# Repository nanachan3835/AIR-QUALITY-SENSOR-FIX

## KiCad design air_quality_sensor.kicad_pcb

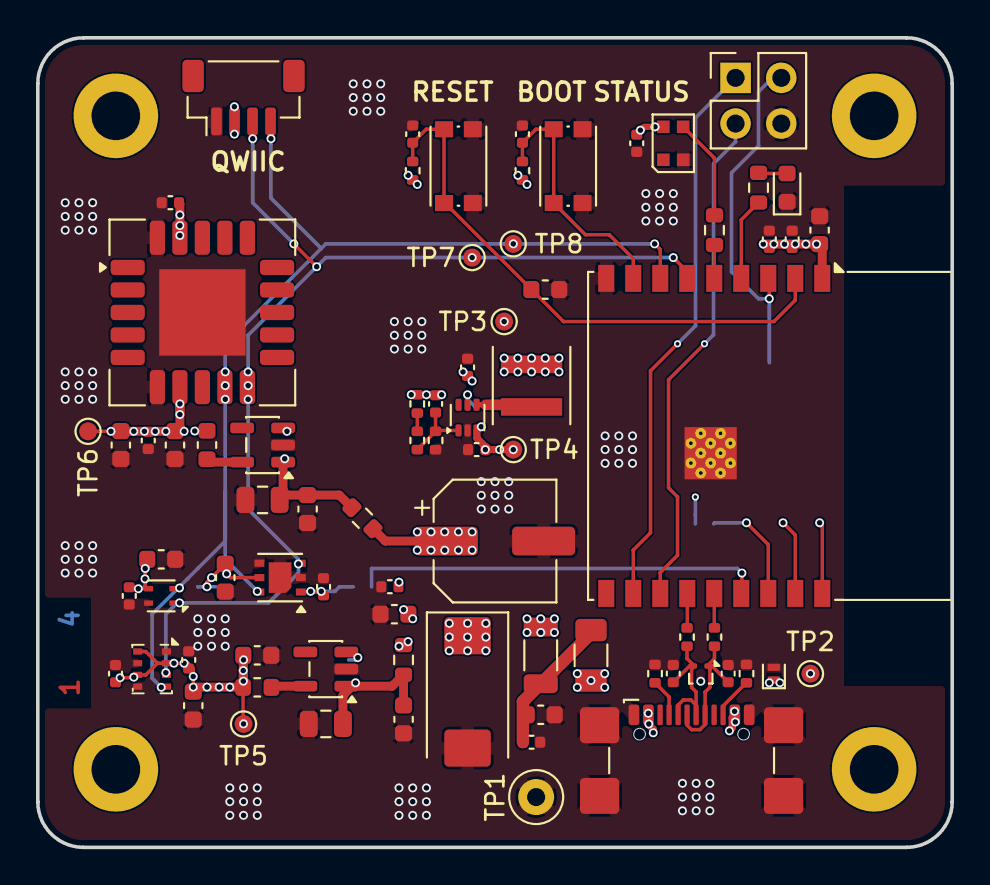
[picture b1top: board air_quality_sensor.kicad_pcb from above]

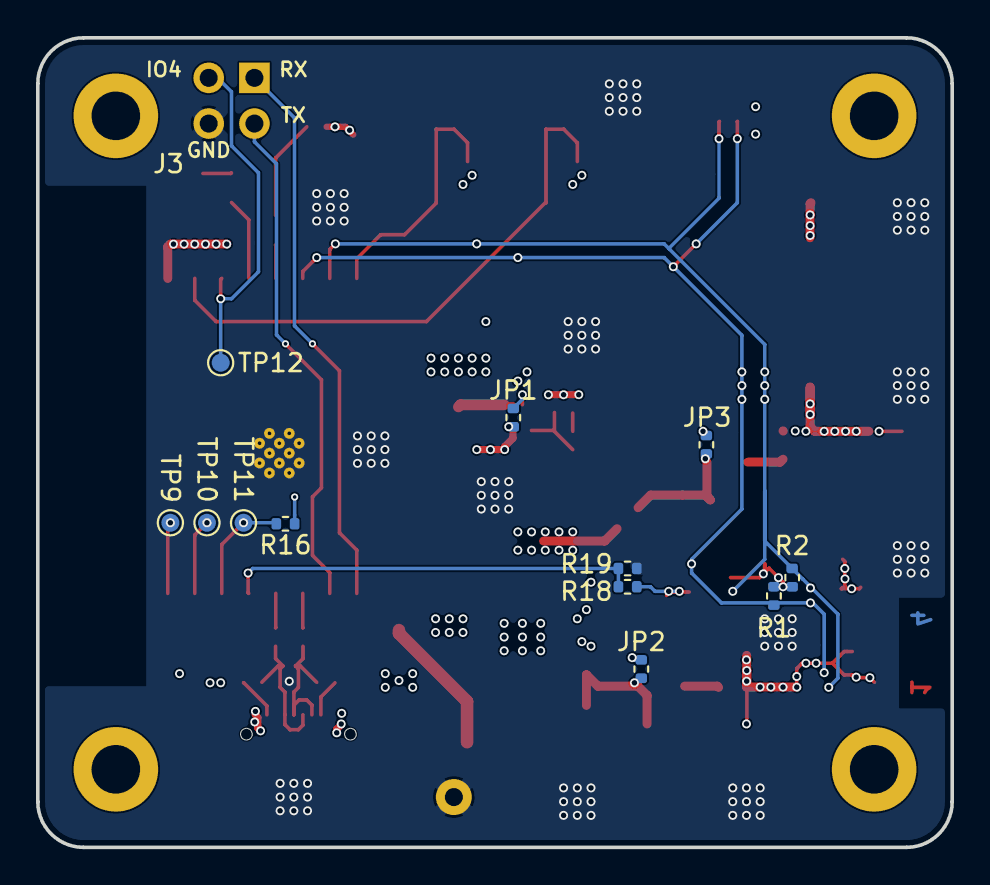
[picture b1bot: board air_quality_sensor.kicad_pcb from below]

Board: 4 copper layers, 50.8 x 45.0 mm, 93 parts (12 on the bottom side), 38 nets.

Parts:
C1: 4.7µ/10V/X5R; C_0402_1005Metric
C2, C3, C5, C12, C13, C21, C22, C25, C30, C31, C34: 100n/10V/X5R; C_0402_1005Metric
C4, C9, C10: 10p/10V/C0G; C_0402_1005Metric
C6, C29: 22µ/10V/X5R; C_0402_1005Metric
C7, C8, C11, C17, C18, C19, C20, C24, C26, C28, C32, C33: 1µ/10V/X5R; C_0603_1608Metric
C14, C27: 47µ/10V/X5R; C_0805_2012Metric
C15: 100µ/16V; CP_EIA-7343-20_Kemet-V
C16: 1µ/10V/X5R; C_0402_1005Metric
C23: 47u/16V/20%; CP_Elec_6.3x7.7
D1: ESDALC5; D_SOD-882
D2: LED 0603 red; LED_0603_1608Metric
D3: WS2812; LED_WS2812B-2020_PLCC4_2.0x2.0mm
F1: PPTC 8V 750mA; Fuse_1206_3216Metric
FB1, FB3: 0R; L_0603_1608Metric
FB2: 1k@100MHz; L_1206_3216Metric
H1, H2, H3, H4: M3_MountingHole; MountingHole_2.7mm_M2.5_DIN965_Pad
J1: USB4110; USB_C_Receptacle_GCT_USB4110
J2: QWIIC Connector; JST_SH_BM04B-SRSS-TB_1x04-1MP_P1.00mm_Vertical
J3: Conn_02x02_Odd_Even; PinHeader_2x02_P2.54mm_Vertical
JP1, JP2, JP3: 0/1%; R_0402_1005Metric
L1: 1uH/20%/9.6A; L_Coilcraft_XxL4020
R1, R2: 4.7k/1%; R_0402_1005Metric
R3, R9: 22/1%; R_0402_1005Metric
R4, R5: 5.1k/1%; R_0402_1005Metric
R6: 270k/1%; R_0402_1005Metric
R7: 180k/1%; R_0402_1005Metric
R8: 100k/1%; R_0402_1005Metric
R10, R12: 330/1%; R_0603_1608Metric
R11: 36/1%; R_0603_1608Metric
R13: 0/1%; R_0603_1608Metric
R14, R15, R18, R19: 10k/1%; R_0402_1005Metric
R16: 10K; R_0402_1005Metric
SW1, SW2: Push_Button; SW_Push_1P1T_NO_CK_KMR2
TP1: GND; TestPoint_Loop_D2.50mm_Drill1.0mm
TP2: VBUS; TestPoint_Pad_D1.0mm
TP3: +3V3; TestPoint_Pad_D1.0mm
TP4: 5V; TestPoint_Pad_D1.0mm
TP5: +3V3_SENS; TestPoint_Pad_D1.0mm
TP6: 3V3_SCD; TestPoint_Pad_D1.0mm
TP7: SDA; TestPoint_Pad_D1.0mm
TP8: SCL; TestPoint_Pad_D1.0mm
TP9: IO0; TestPoint_Pad_D1.0mm
TP10: IO1; TestPoint_Pad_D1.0mm
TP11: IO2; TestPoint_Pad_D1.0mm
TP12: ADC1_CH4; TestPoint_Pad_D1.0mm
U1: TLV62569A; SOT-563
U2: SHT40; Sensirion_DFN-4_1.5x1.5mm_P0.8mm_SHT4x_NoCentralPad
U3: BMP280; Bosch_LGA-8_2x2.5mm_P0.65mm_ClockwisePinNumbering
U4: TPD2EUSB30; Texas_DRT-3
U5: SCD41; Sensirion_SCD4x-1EP_10.1x10.1mm_P1.25mm_EP4.8x4.8mm
U6: SGP41; XDCR_SGP41-D-R4
U7: TPS7A20; SOT-23-5
U8: ESP32-C3-WROOM-02
U9: TLV75533P; SOT-23-5

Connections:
+3V3: C6.1, C10.1, C29.1, C31.1, C33.1, J2.2, L1.2, R6.1, R14.1, R15.1, R16.1, TP3.1 (1_1), U8.1 (3V3)
+3V3_SCD: C13.1, C18.1, C32.1, C34.1, FB1.2, TP6.1 (1_1), U5.7 (VDD), U5.19 (VDD)
+3V3_SENS: C2.1, C3.1, C5.1, C7.1, C8.1, C16.1, C20.1, C24.1, FB3.2, R1.1, R2.1, R18.1, TP5.1 (1_1), U2.3 (VDD), U3.2 (CSB), U3.6 (VDDIO), U3.8 (VDD), U6.1 (VDD), U6.5 (VDDH)
+5V: C1.1, C15.1, C19.1, C21.1, C22.1, C23.1, D3.4 (VDD), FB2.2, JP1.1 (A), R11.1, R13.1, TP4.1 (1_1), U1.3 (VIN)
/ESP32_ADC1_CH3: R18.2, R19.1, U8.15 (IO3)
/ESP32_ADC1_CH4: J3.2, TP12.1 (1_1), U8.3 (IO4)
/ESP32_BOOT_SEL: C30.1, R15.2, SW2.2, U8.8 (IO9)
/ESP32_EN: C25.1, C26.1, R14.2, SW1.2, U8.2 (EN)
/ESP32_EN_LED: R10.1, U8.4 (IO5)
/ESP32_NEOP_DIN: R12.1, U8.5 (IO6)
/ESP32_RX: J3.1, U8.11 (IO20/RXD)
/ESP32_SCL: J2.4, R2.2, TP8.1 (1_1), U2.2 (SCL), U3.4 (SCK), U5.9 (SCL), U6.6 (SCL), U8.7 (IO8)
/ESP32_SDA: J2.3, R1.2, TP7.1 (1_1), U2.1 (SDA), U3.3 (SDI), U5.10 (SDA), U6.3 (SDA), U8.6 (IO7)
/ESP32_TX: J3.3, U8.12 (IO21/TXD)
/ESP32_USB_D+: R3.2, U8.14 (IO19)
/ESP32_USB_D-: R9.2, U8.13 (IO18)
/USB_D+: C4.1, J1.A6 (D+), J1.B6 (D+), R3.1, U4.1 (D+)
/USB_D-: C9.1, J1.A7 (D-), J1.B7 (D-), R9.1, U4.2 (D-)
GND: C1.2, C2.2, C3.2, C4.2, C5.2, C6.2, C7.2, C8.2, C9.2, C11.2, C12.2, C13.2, C14.2, C15.2, C16.2, C17.2, C18.2, C19.2, C20.2, C21.2, C22.2, C23.2, C24.2, C25.2, C26.2, C27.2, C28.2, C29.2, C30.2, C31.2, C32.2, C33.2, C34.2, D1.2 (A), D2.1 (K), D3.2 (VSS), J1.A1 (GND), J1.A12 (GND), J1.B1 (GND), J1.B12 (GND), J1.S1 (SHIELD), J2.1, J3.4, R4.2, R5.2, R8.2, R19.2, SW1.1, SW2.1, TP1.1 (1_1), U1.2 (GND), U2.4 (VSS), U3.1 (GND), U3.5 (SDO), U3.7 (GND), U4.3 (GND), U5.6 (GND), U5.20 (GND), U5.21 (GND), U6.2 (VSS), U6.4 (N/A), U6.7 (EP), U7.2 (GND), U8.9 (GND), U8.19 (GND), U9.2 (GND)
unnamed: C11.1, C12.1, F1.2, FB2.1
unnamed: D2.2 (A), R10.2
unnamed: D3.3 (DIN), R12.2
unnamed: J1.A5 (CC1), R4.1
unnamed: J1.B5 (CC2), R5.1
unnamed: JP1.2 (B), U1.5 (EN)
unnamed: C14.1, C17.1, JP2.1 (A), R11.2, U7.1 (IN)
unnamed: JP2.2 (B), U7.3 (EN)
unnamed: C27.1, C28.1, JP3.1 (A), R13.2, U9.1 (IN)
unnamed: JP3.2 (B), U9.3 (EN)
unnamed: R6.2, R7.1
unnamed: C10.2, R7.2, R8.1, U1.1 (FB)
unnamed: L1.1, U1.4 (SW)
unnamed: FB3.1, U7.5 (OUT)
unnamed: TP9.1 (1_1), U8.18 (IO0)
unnamed: TP10.1 (1_1), U8.17 (IO1)
unnamed: R16.2, TP11.1 (1_1), U8.16 (IO2)
unnamed: FB1.1, U9.5 (OUT)
VBUS: D1.1 (K), F1.1, J1.A4 (VBUS), J1.A9 (VBUS), J1.B4 (VBUS), J1.B9 (VBUS), TP2.1 (1_1)

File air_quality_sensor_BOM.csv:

"Reference","Qty","DNP","Footprint","Manufacturer (MFR)","Value","Manufacturer Part Number (MPN)","Datasheet","Comments"
"C1","1","","Capacitor_SMD:C_0402_1005Metric","KYOCERA AVX","4.7µ/10V/X5R","0402ZD475KAT2A","",""
"C2,C3,C5,C12,C13,C21,C22,C25,C30,C31,C34","11","","Capacitor_SMD:C_0402_1005Metric","YAGEO","100n/10V/X5R","CC0402KPX5R6BB104","",""
"C4,C9","2","","Capacitor_SMD:C_0402_1005Metric","KEMET","10p/10V/C0G","C0402C100J8GACTU","",""
"C6,C29","2","","Capacitor_SMD:C_0402_1005Metric","Murata","22µ/10V/X5R","GRM158R61A226ME15D","",""
"C7,C8,C11,C17,C18,C19,C20,C24,C26,C28,C32,C33","12","","Capacitor_SMD:C_0603_1608Metric","YAGEO","1µ/10V/X5R","CC0603KRX5R6BB105","",""
"C10","1","DNP","Capacitor_SMD:C_0402_1005Metric","KEMET","10p/10V/C0G","C0402C100J8GACTU","",""
"C14,C27","2","","Capacitor_SMD:C_0805_2012Metric","Murata","47µ/10V/X5R","GRM21BR61A476ME15L","",""
"C15","1","","Capacitor_Tantalum_SMD:CP_EIA-7343-20_Kemet-V","Kyocera AVX","100µ/16V","TCJY107M016R0050","",""
"C16","1","","Capacitor_SMD:C_0402_1005Metric","YAGEO","1µ/10V/X5R","CC0402KPX5R6BB104","",""
"C23","1","","Capacitor_SMD:CP_Elec_6.3x7.7","Panasonic","47u/16V/20%","EEE-HC1E470XP","",""
"D1","1","","Diode_SMD:D_SOD-882","ST Microelectronics","ESDALC5","ESDALC5-1BM2","kicad-embed://esdalc5-1bm2.pdf",""
"D2","1","","LED_SMD:LED_0603_1608Metric","LITEON","LED 0603 red","LTST-C190EKT","https://www.mouser.com/catalog/specsheets/lite-on_lites05751-1.pdf",""
"D3","1","","LED_SMD:LED_WS2812B-2020_PLCC4_2.0x2.0mm","Worldsemi","WS2812","WS2812B-2020","https://cdn-shop.adafruit.com/product-files/4684/4684_WS2812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",""
"F1","1","","Fuse:Fuse_1206_3216Metric","Littelfuse","PPTC 8V 750mA","1206L075THYR","https://www.littelfuse.com/assetdocs/resettable-ptcs-1206l-d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",""
"FB1,FB3","2","","Inductor_SMD:L_0603_1608Metric","Murata Electronics","1k@100MHz","BLM18KG102SN1D","https://www.lcsc.com/datasheet/C160982.pdf",""
"FB2","1","","Inductor_SMD:L_1206_3216Metric","Murata Electronics","1k@100MHz","BLM31KN102SH1L","https://www.mouser.de/datasheet/3/76/1/QNFA9148.pdf",""
"J1","1","","Connector_USB:USB_C_Receptacle_GCT_USB4110","GCT","USB4110","USB4110-GF-A ","https://www.usb.org/sites/default/files/documents/usb_type-c.zip",""
"J2","1","","Connector_JST:JST_SH_BM04B-SRSS-TB_1x04-1MP_P1.00mm_Vertical","JST","QWIIC Connector","BM04B-SRSS-TB(LF)(SN)","",""
"JP1,JP2,JP3","3","","Resistor_SMD:R_0402_1005Metric","","0/1%","","",""
"L1","1","","Inductor_SMD:L_Coilcraft_XxL4020","Coilcraft","1uH/20%/9.6A","XEL4020-102MEC","https://4donline.ihs.com/images/VipMasterIC/IC/COLC/COLC-S-A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",""
"R1,R2","2","","Resistor_SMD:R_0402_1005Metric","","4.7k/1%","","",""
"R3,R9","2","","Resistor_SMD:R_0402_1005Metric","","22/1%","","",""
"R4,R5","2","","Resistor_SMD:R_0402_1005Metric","","5.1k/1%","","",""
"R6","1","","Resistor_SMD:R_0402_1005Metric","","270k/1%","","",""
"R7","1","","Resistor_SMD:R_0402_1005Metric","","180k/1%","","",""
"R8","1","","Resistor_SMD:R_0402_1005Metric","","100k/1%","","",""
"R10,R12","2","","Resistor_SMD:R_0603_1608Metric","","330/1%","","",""
"R11","1","","Resistor_SMD:R_0603_1608Metric","","36/1%","","",""
"R13","1","","Resistor_SMD:R_0603_1608Metric","","0/1%","","",""
"R14,R15,R18,R19","4","","Resistor_SMD:R_0402_1005Metric","","10k/1%","","",""
"SW1,SW2","2","","Button_Switch_SMD:SW_Push_1P1T_NO_CK_KMR2","C&K","Push_Button","KMR621NG_LFS","https://www.ckswitches.com/media/1907/kmr6.pdf",""
"U1","1","","Package_TO_SOT_SMD:SOT-563","Texas Instruments","TLV62569A","TLV62569ADRLT","https://www.ti.com/lit/gpn/tlv62569a",""
"U2","1","","Sensor_Humidity:Sensirion_DFN-4_1.5x1.5mm_P0.8mm_SHT4x_NoCentralPad","Sensirion","SHT40","SHT40-AD1B-R2","https://www.mouser.de/datasheet/3/1278/1/HT_DS_Datasheet_SHT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",""
"U3","1","","Package_LGA:Bosch_LGA-8_2x2.5mm_P0.65mm_ClockwisePinNumbering","Bosch Sensortec","BMP280","BMP280","https://cdn-shop.adafruit.com/datasheets/BST-BMP280-DS001-11.pdf",""
"U4","1","","Package_TO_SOT_SMD:Texas_DRT-3","Texas Instruments","TPD2EUSB30","TPD2EUSB30DRTR","http://www.ti.com/lit/ds/symlink/tpd2eusb30a.pdf",""
"U5","1","","Sensor:Sensirion_SCD4x-1EP_10.1x10.1mm_P1.25mm_EP4.8x4.8mm","Sensirion","SCD41","SCD41-D-R2","https://sensirion.com/media/documents/E0F04247/631EF271/CD_D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","very temperature sensitive! Use low-temp solder paste!"
"U6","1","","air_quality_footprints:XDCR_SGP41-D-R4","Sensirion","SGP41","SGP41-D-R4","https://sensirion.com/media/documents/5FE8673C/61E96F50/Sens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",""
"U7","1","","Package_TO_SOT_SMD:SOT-23-5","Texas Instruments","TPS7A20","TPS7A2033PDBVR","https://www.ti.com/lit/ds/symlink/tps7a20.pdf",""
"U8","1","","RF_Module:ESP32-C3-WROOM-02","Espressif","ESP32-C3-WROOM-02","ESP32-C3-WROOM-02","https://www.espressif.com/sites/default/files/documentation/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",""
"U9","1","","Package_TO_SOT_SMD:SOT-23-5","Texas Instruments","TLV75533P"," TLV75533PDBVR","https://www.ti.com/lit/ds/symlink/tlv755p.pdf","Alternative: Diodes Inc. AP2112K-3.3TRG1 "
